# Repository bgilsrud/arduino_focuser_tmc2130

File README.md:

# Arduino-based telescope focuser controller
Simple MoonLite-compatible focuser controller. Thought to be used with INDI.
Does not support temperature compensation yet (feel free to fork!).
It also adds a function to the MoonLite protocol (non-official command) to
change the state of the Arduino's digital and PWM pins.

### Overview
This MoonLite focuser uses an Arduino (Nano, in my case) to control
a stepper motor that moves the focuser knob using a belt.
There are also MOSFETS (think of them like relays) that are able to
control dew heaters or fans to cool your primary mirror.

<br>

### AstroAllInOne
<a href="https://github.com/SquareBoot/AstroAllInOne">AstroAllInOne</a>
is this firmware's companion INDI driver that allows the end user to
change the state of **every** pin of the board (pay attention! **do not change the
state of the stepper motor driver's pins**). Refer to its documentation on
how to configure it. Without AstroAllInOne, the Arduino will behave just like
a generic MoonLite focuser.<br>

### Autodesk Eagle project
In the "Eagle" directory there is the full circuit project, both schematics and PCB. 
It's the one I use for my telescope, but of course you can modify it to 
accomplish your necessities: for instance, you could add another dew heater port, 
or remove the Newton mirror cooler MOSFET. Refer to the AstroAllInOne readme on 
how to define new digital or PWM pins definitions.
<br>**Made with Eagle 9.0.1 Premium**<br>

### Mounting brackets
Also includes mounting brackets for the common SkyWatcher 
dual-speed Crayford focuser (made for my 200mm Newton OTA).
**AutoCAD 2016** project and STL 3D exported file.

### Forking & issues
Feel free to submit pull requests and open issues! Also new brackets are welcome!

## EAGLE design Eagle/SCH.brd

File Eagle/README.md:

# Autodesk Eagle CAD schematics
Circuit & PCB. Please use the given DRV8825 library. Installing further Eagle libraries may be necessary, so please open the schematic, open the "Add component" window and click on "Open Library Manager". Then, in the "Available" section install all the available libraries from Seed and Sparkfun. Enjoy!

### Made with Eagle 8.7.1 Premium

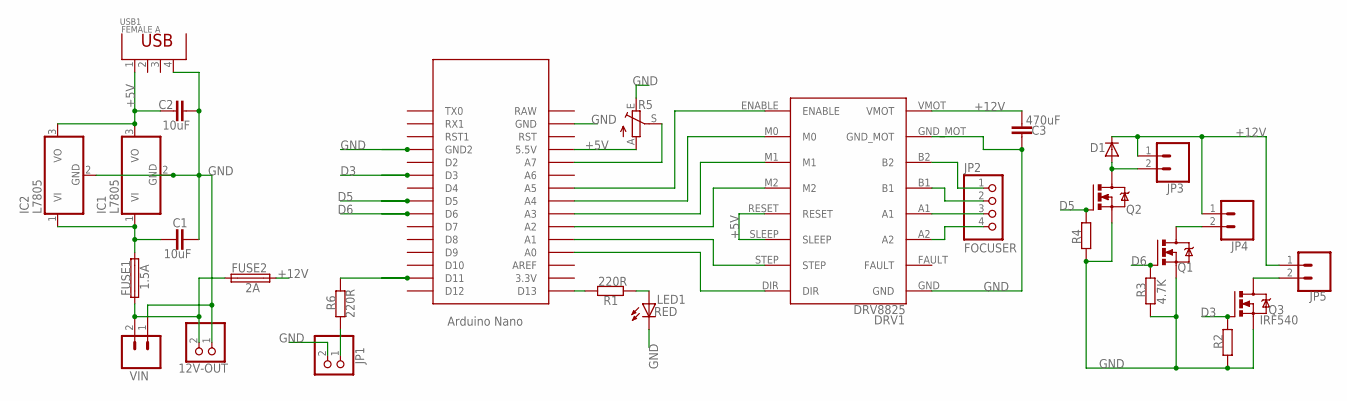
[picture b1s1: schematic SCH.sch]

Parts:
12V-OUT: PINHD-1X2; 1X02
C1, C2: 10uF; C025-024X044
C3: 470uF; C5B2.5
D1: DIODE-D-2.5; D-2.5
DRV1: DRV8825
FUSE1: 1.5A; FUSE_HOLDER_5X20MM
FUSE2: 2A; FUSE_HOLDER_5X20MM
IC1, IC2: L7805; TO220V
JP1: PINHD-1X2; 1X02
JP2: FOCUSER; 1X04
JP3, JP4, JP5: CONN_025MM; SCREWTERMINAL-5MM-2
LED1: RED; LED3MM
Q1, Q2, Q3: IRF540; TO220BV
R1, R6: 220R; 0204/5
R2, R3, R4: 4.7K; 0204/5
R5: TRIM_EU-B64Y; B64Y
U$1: NANO
USB1: FEMALE A; USB4+2P-2.0-90D
VIN: CONN_025MM; SCREWTERMINAL-5MM-2

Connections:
+5V: C2.1, DRV1.RESET, DRV1.SLEEP, IC1.3 (VO), IC2.3 (VO), R5.A, U$1.5V (5.5V), USB1.1
+12V: C3.2, D1.C, DRV1.VMOT, FUSE2.2, JP3.1, JP4.1, JP5.1
D3: Q3.G, R2.2, U$1.D3
D5: Q2.G, R4.2, U$1.D5
D6: Q1.G, R3.2, U$1.D6
D13: R1.2, U$1.D13
GND: 12V-OUT.1, C1.2, C2.2, C3.1, DRV1.GND, DRV1.GND_MOT, IC1.2 (GND), IC2.2 (GND), JP1.2, LED1.K (C), Q1.S, Q2.S, Q3.S, R2.1, R3.1, R4.1, R5.E, U$1.GND, U$1.GND1 (GND2), USB1.4, VIN.1
unnamed: LED1.A, R1.1
unnamed: R5.S, U$1.A7
unnamed: R6.2, U$1.D11
unnamed: C1.1, FUSE1.2, IC1.1 (VI), IC2.1 (VI)
unnamed: DRV1.DIR, U$1.A0
unnamed: DRV1.ENABLE, U$1.A5
unnamed: 12V-OUT.2, FUSE1.1, FUSE2.1, VIN.2
unnamed: D1.A, JP3.2, Q2.D
unnamed: JP4.2, Q1.D
unnamed: JP5.2, Q3.D
unnamed: DRV1.STEP, U$1.A1
unnamed: DRV1.B2, JP2.1
unnamed: DRV1.B1, JP2.2
unnamed: DRV1.A1, JP2.3
unnamed: DRV1.A2, JP2.4
unnamed: DRV1.M2, U$1.A2
unnamed: DRV1.M1, U$1.A3
unnamed: JP1.1, R6.1
unnamed: DRV1.M0, U$1.A4

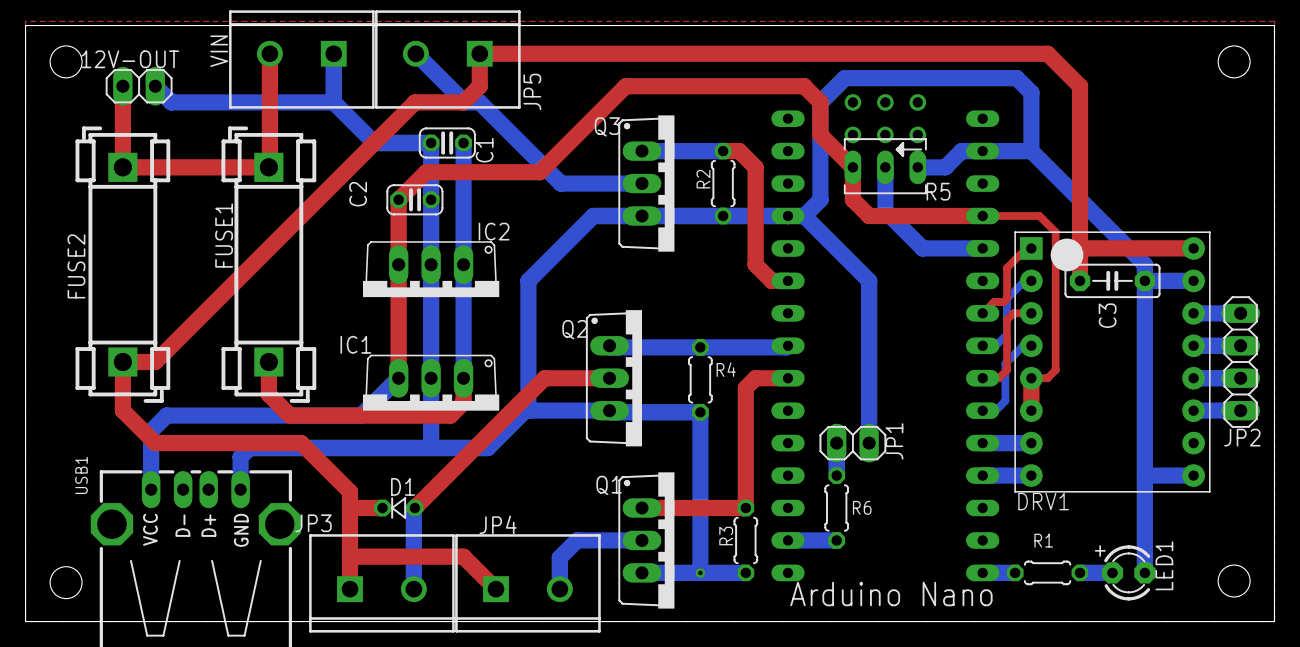
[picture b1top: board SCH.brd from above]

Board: 2 copper layers, 97.8 x 46.7 mm, 28 parts (0 on the bottom side), 26 nets.

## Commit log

2018-02-26 Update
    Code reformat, new readme
2018-02-26 Added drawings
2018-02-26 Arduino code rewritten to work with StepSticks
    I changed almost everything...
2018-02-27 Updated brackets
2018-03-30 Added Eagle files, new brackets, Arduino firmware update
2018-04-01 Move sketch to appropriately named subfolder
    The Arduino IDE requires that a sketch be located in a folder of the same name. Although the name of the repository does match the sketch name, when GitHub's popular Clone or download > Download ZIP 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
    When opening a file that does not meet this sketch/folder name matching requirement the Arduino IDE presents a dialog:
    The file "Arduino-MoonLite-focuser.ino" needs to be inside a sketch folder named "Arduino-MoonLite-focuser".
    Create this folder, move the file, and continue?
    After clicking "OK" the Arduino IDE currently moves
2018-04-01 Added README, LICENSE, brackets updated
2018-06-17 Added photos, Arduino SW update
2018-09-22 New PCB design
2018-09-22 PCB ground plane added
2018-09-22 Update PCB
2018-11-02 Backlink to CADLAB.io has been added.
2018-11-02 Revert "Backlink to CADLAB.io has been added."
    This reverts commit 1e0c467e5ff5a30cccea21821133fbd6f68ef656.
2018-11-02 Update with new brackets
2018-11-02 Backlight cmd
2022-03-27 TMC2130 support
2022-04-01 fix irun, scale steps, fix limit

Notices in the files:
parts and their libraries:
SparkFun-Connectors: Licensing: Creative Commons ShareAlike 4.0 International - https://creativecommons.org/licenses/by-sa/4.0
